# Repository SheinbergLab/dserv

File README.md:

# dserv

## Overview

dserv is a real-time datapoint server for experimental control and data acquisition. At its core is a shared datapoint store (the "bus") implemented in C/C++ that acts as the central communication hub. Attached subprocesses, each running an isolated Tcl interpreter, can listen to, subscribe to, update, and react to changes in datapoints on the bus. This architecture provides extensive scriptability while retaining high-performance C/C++ internals.

All dserv instances include built-in HTTP and WebSocket support. Each instance advertises itself on its own link as a `_dserv._tcp` DNS-SD service (mDNS, via the OS responder) and heartbeats to a workgroup registry for discovery off-link; see `docs/discovery.md`. Web dashboards provide inspection and control of active systems.

## Architecture

```
                        ┌──────────────────────────┐
                        │     Datapoint Store      │
                        │        (the bus)         │
                        └───┬───┬───┬───┬───┬──────┘
                            │   │   │   │   │
               ┌─────────┬──┘   │   │   │   └──┬──────────┐
               │         │      │   │   │      │          │
            ┌──┴──┐  ┌───┴──┐ ┌─┴─┐ │ ┌─┴──┐ ┌─┴──┐  ┌───┴───┐
            │ ess │  │ mesh │ │ em│ │ │stim│ │ df │  │configs│
            └─────┘  └──────┘ └───┘ │ └────┘ └────┘  └───────┘
                                    │
                          ... more subprocesses ...
```
Datapoints are generic data stores that can point to one or more elements of a particular datatype (bytes, short and long integers, strings, floating point and double precision numbers, images, etc. 

Each subprocess is an isolated Tcl interpreter that has direct shared memory access to the datastore. Subprocesses can send messages to other subprocesses and communicate with remote dserv instances over TCP/IP. The startup configuration (`config/dsconf.tcl`) launches the standard set of subprocesses for experiment control, data management, mesh networking, and more.

### Core (`src/`)

The C/C++ core provides:
- **Datapoint store**: thread-safe key-value store with publish/subscribe semantics
- **Datapoint processors**: native C plugins for low-latency datapoint transformations
- **TclServer**: embedded Tcl interpreters for each subprocess with access to the bus
- **HTTP/WebSocket server**: built-in web server for GUIs and API access

### Modules (`modules/`)

Loadable shared libraries that extend subprocess capabilities with hardware and system integration:

| Module | Description |
|--------|-------------|
| `ain` | Analog input |
| `camera` | Camera capture (libcamera) |
| `eventlog` | Event logging |
| `gpio_input` / `gpio_output` | GPIO pin control |
| `ina226` | Power/current monitoring |
| `joystick4` | Joystick input |
| `juicer` | Pump/reward control |
| `mesh` | Mesh network communication |
| `rmt` | Remote stimulus display control |
| `sound` | Audio playback |
| `timer` | Precision timing |
| `touch` | Touchscreen input |
| `usbio` | USB I/O devices |

### Processors (`processors/`)

Native C plugins loaded into the datapoint bus for fast, low-latency processing. These run in the bus thread itself and are used for tasks that require deterministic timing:

- **windows / touch_windows**: define virtual spatial windows and track entry/exit events for eye or touch position data
- **sampler**: datapoint sampling/decimation
- **in_out**: binary region membership testing
- **up_down_left_right**: directional movement detection

### Configuration (`config/`)

Tcl scripts that configure and launch subprocesses. `dsconf.tcl` is the main startup script that initializes the system, loading subprocesses for experiment control (`ess`), eye tracking (`em`), reward delivery (`juicer`), stimulus control (`stim`), data file management (`df`), mesh networking (`mesh`), and others.

### Localization (`local/`)

Local configuration files allow each instance to be customized depending on attached hardware or software requirements. The `local/` folder includes example `.tcl` configuration files that can be copied and customized (removing the .EXAMPLE suffix). These will be maintained across dserv updates.

### Web Interfaces (`www/`)

Browser-based GUIs served by the built-in HTTP server:

- **Dashboard** (`index.html`) - system overview and terminal access
- **ESS Control** (`ess_control.html`) - experiment state system control
- **ESS Workbench** (`ess_workbench.html`) - experiment design and monitoring
- **Data Manager** (`data_manager.html`) - data file management
- **DG Table Viewer** (`DGTableViewer.html`) - data group inspection
- **StimDG Viewer** (`stimdg_viewer.html`) - stimulus data group viewer
- **Event Viewer** (`event_viewer.html`) - real-time event stream
- **Explorer** (`explorer.html`) - datapoint browser
- **Terminal** (`terminal.html`) - Tcl command terminal
- **Tutorial** (`tutorial.html`) - interactive tutorial

Available web interfaces can be accessed based on the names above, as in:

-* http://localhost:2565/ (gui)
-* http://localhost:2565/terminal
-* http://localhost:2565/explorer

### dserv-agent (`dserv-agent/`)

A complementary Go service that provides out-of-band management for dserv systems. Key capabilities:

- **Mesh registry**: aggregates the heartbeats of every dserv in a workgroup, so instances can be found from off-link (on-link discovery is mDNS, see `docs/discovery.md`)
- **Script browsing**: browse and manage experiment scripts
- **Registry mode**: agents can run as registries that store and serve experiment scripts for connected dserv systems
- **Service management**: start/stop/restart dserv, install updates, and monitor health even when dserv is down

### dservctl CLI (`tools/dservctl`)

A command line program called `dservctl` provides a single executable (written in Go) that can be run from the terminal to interact with the dserv process and other subprocesses and to retrieve and update scripts on a dserv-agent registry server. Extensive help is available by running `dservctl --help`.

## Default Endpoints

| Port | Service |
|------|---------|
| 2560 | dserv TCP/IP message port |
| 2565 | dserv WebSocket (dashboard + GUIs) |

## Git Submodules

This repo uses [git submodules](https://git-scm.com/book/en/v2/Git-Tools-Submodules) for several dependencies:
 - [tcl](https://github.com/tcltk/tcl) 9
 - [jansson](https://github.com/akheron/jansson) JSON
 - [FLTK](https://github.com/fltk/fltk) GUI framework

To clone with submodules:

```
git clone --recurse-submodules https://github.com/SheinbergLab/dserv.git
```

To update submodules in an existing clone:

```
git submodule update --init --recursive
git pull --recurse-submodules
```

## Building

dserv uses CMake:

```
mkdir build && cd build
cmake ..
make
```

## Releases with GitHub Actions

This repo uses GitHub Actions to build and test on push, and to create releases on tag push. To release:

```
git tag -a 0.0.2 -m "Release description"
git push --tags
```

See [package_and_release.yml](./.github/workflows/package_and_release.yml) for workflow details and [Releases](https://github.com/SheinbergLab/dserv/releases) for artifacts.

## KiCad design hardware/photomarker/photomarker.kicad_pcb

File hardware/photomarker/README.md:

# Stimulus onset photo-marker

Sheinberg Lab — **rev A**

A per-rig photodiode board that timestamps stimulus light onset two ways at once:
an **analog waveform** into an MCP3204 channel, and a **comparator edge** into a
dserv DI pin (IRQ-latched with a box-clock stamp, so it beats the ~100 µs ADC
scan quantization).

Wire both. The digital edge is your routine per-trial timestamp; the analog
trace is how you verify the edge means what you think, because a fixed voltage
threshold lands at a different fraction of the transition for black→white than
for a gray-to-gray change.

- **50 × 34 mm**, 2-layer, M3 mounts on a **40 × 24 mm** pattern
- Silkscreen carries the lab name and **rev**; bump `REV` in `gen_photomarker.py`
- **DRC clean**: 0 violations, 0 unconnected (KiCad 10.0.4)
- Photodiode die centre is at board-local **(14, 17) mm**, marked with a
  crosshair on both silkscreens so an aperture or hood can be aligned to it

## Regenerating

The board is generated, not hand-drawn. Edit `gen_photomarker.py` (placement
table + routing table near the top) and re-run:

```bash
/Applications/KiCad/KiCad.app/Contents/Frameworks/Python.framework/Versions/3.9/bin/python3 gen_photomarker.py
```

Two API gotchas baked into the script, both found the hard way:
`board.Add(fp)` **must precede** `fp.Flip()` (flipping an unparented footprint
segfaults), and the flip is an **X-mirror** — verified empirically rather than
assumed.

## Board sides

**Top faces the screen.** Only the OPT101 is up there, standing 4.19 mm proud so
nothing shadows it.

**Bottom carries all SMD** — single-sided assembly at JLCPCB, and the board
itself blocks the bring-up LED's light from reaching the photodiode.

## Ordering

Upload `fab/photomarker-gerbers.zip`. For assembly add
`fab/photomarker-cpl.csv` and `fab/photomarker-bom.csv`.

**The BOM's `LCSC Part #` column is deliberately empty.** Fill it from JLCPCB's
parts search — do not trust a guessed C-number, it orders the wrong part.

JLCPCB places **10 parts**: U2, R1–R5, R11, C1–C3. Everything else is DNP or
hand-soldered. At that count, hand-soldering a SOIC-8 and nine 0805s may well
cost less than the assembly setup fee — worth pricing both ways.

### You solder these yourself

| Ref | Part | Note |
|-----|------|------|
| U1 | OPT101, DIP-8 | Mount from the **top**. Strap pin 4 (1M) to pin 5 (OUT) is on the PCB already. |
| J1 | JST-PH B5B-PH-K, 5-pin vertical | On the bottom, so the cable exits away from the screen. |

**OPT101 handling:** TI warns the clear plastic is moisture-sensitive and that
rapid heating can stress the wire bonds. If the parts have sat in humidity, bake
at 85 °C for 24 h first. Solder gently either way.

## Connector J1

Pin 1 is leftmost. Silkscreen reads `3V3 GND AO DIb DIa`.

| Pin | Net | To the extio box |
|-----|-----|------------------|
| 1 | +3V3 | 3V3 |
| 2 | GND | GND |
| 3 | AOUT | MCP3204 **CH2** (CH0/CH1 are the joystick) |
| 4 | DI-B | free GPIO — optional second threshold |
| 5 | DI-A | free GPIO — **main onset edge** |

Free GPIOs per `wiznet-io/PINMAP.md`: 9–14, 26, 27.

**Output goes LOW on light onset** (signal on IN−), so configure that DI for the
falling edge.

On the `ain` group carrying CH2: set `deadband 0` and `average 1`. Both smear
the edge, which is the one thing you are trying to measure.

## Design values

Threshold network on 3.3 V, R1 = 39 k, R2 = 10 k, R3 = 270 k:

- Onset threshold **0.749 V**, release **0.654 V**, hysteresis **94 mV**
- Input filter R4/C3 = 10 k / 3.3 nF → **4.8 kHz**, τ = 33 µs

Because the signal is on IN−, **the hysteresis lands entirely on the release
side** — it costs nothing on the onset edge, so be generous with it.

Aim the threshold at **~50 % of your lit-state level**, not 20 %. Mid-transition
is steepest, so timing there is least sensitive to stimulus amplitude drift. The
resulting latency to true onset is a constant: measure it once off the analog
trace and subtract.

Retune by swapping R1 alone:

| R1 | Onset | Hysteresis |
|----|-------|-----------|
| 68 k | 0.513 V | 103 mV |
| **39 k** | **0.749 V** | **94 mV** |
| 27 k | 0.955 V | 87 mV |
| 18 k | 1.228 V | 77 mV |
| 12 k | 1.536 V | 65 mV |

C3 must be **C0G/NP0**, not X7R — X7R drifts with temperature and DC bias, which
would move the filter corner and turn your calibrated constant lag into a
drifting one.

## U2: TLV3202 or LM393

The footprint is SOIC-8 and the two parts are pin-identical
(1=OUT_A, 2=IN_A−, 3=IN_A+, 4=GND, 5=IN_B+, 6=IN_B−, 7=OUT_B, 8=VCC).

- **TLV3202** (recommended): push-pull, 5 mV max offset. Leave R7/R14 unfitted.
- **LM393** (fallback): open-collector — **fit R7** (and R14 if using
  comparator B) as pull-ups to 3.3 V.

The LM393's common-mode ceiling (V+ − 1.5 V ≈ 1.8 V at 3.3 V) is not a problem
at this operating point, since the threshold is 0.749 V and the lit level is
~1.5 V by design. There is no 5 V anywhere on the board, so nothing can put 5 V
on a GPIO.

## DNP options

| Ref | Purpose |
|-----|---------|
| R6 | External gain resistor across the OPT101 feedback — **fit this if you saturate**, which is likely at 0.45 V/µW |
| R8 | Parallel with R1 for fine threshold trim |
| R7, R14 | Pull-ups, LM393 only |
| R9, D1 | Bring-up LED on the comparator output. D1 pin 1 = **cathode** (KiCad convention), so the anode faces R9 / +3V3 and the LED lights when the output goes low on light onset |
| R12, R13, R15 | Comparator B's second threshold → DI-B. Populate to time the 25 %→75 % crossing and measure the panel's transition slope in hardware, per trial |
| J2 | 0.1" alternative to J1, same pinout |

**R11 (10 k) is fitted, not DNP.** With the B network unpopulated it pulls
comparator B's IN+ to 3.3 V — definitively above IN−'s ~2.0 V ceiling — so that
comparator parks HIGH instead of oscillating on a floating input, and DI-B
carries a defined level. Re-value it into a real divider with R12 when you
actually want the second threshold.

## Bring-up

Test points: TP1 OPT_OUT, TP2 FILT, TP3 THRESH, TP4 CMP_OUT, TP5 GND.

1. **Cover the sensor.** TP1 should read ~7.5 mV. Mid-scale or railed means the
   part is wrong or damaged.
2. **TP3 should read 0.749 V.**
3. **Point at a white screen.** If TP1 pins at ~2.0 V you are saturated — fit R6,
   mask down to a smaller aperture, or back off.
4. **Check for backlight PWM on the analog channel before trusting anything.** A
   few-hundred-Hz chop cannot be filtered out without wrecking a 2 ms edge. Run
   the panel at 100 % brightness, where most panels stop PWM-ing. Only if you're
   stuck with it, raise C3 to 22 nF (720 Hz, τ = 220 µs) and accept the larger
   constant lag.

## Schematic

`photomarker.kicad_sch` + `schematic.pdf`. **ERC clean (0 violations)**, and verified
against the board by `check_netlist.py` — which compares **nets, refs, values,
footprints and DNP flags**, not just connectivity. All 12 nets match exactly; the
only schematic-side extras are the OPT101's two NC pins, deliberately unconnected
on both sides.

Run it before ordering and after any regeneration (exit status 0 = agreement):

```bash
/Applications/KiCad/KiCad.app/Contents/Frameworks/Python.framework/Versions/3.9/bin/python3 check_netlist.py
```

It is generated by `gen_schematic.py`, which **reads the netlist out of
`photomarker.kicad_pcb`** — so the schematic cannot silently drift from the
board. Regenerate after any board change:

```bash
/Applications/KiCad/KiCad.app/Contents/Frameworks/Python.framework/Versions/3.9/bin/python3 gen_schematic.py
```

Connectivity is by net label rather than drawn wire, with components grouped by
function. That is a deliberate choice for a generated schematic: label
connectivity is verifiable by ERC and by netlist diff, where hand-computed wire
geometry can look connected while being 0.01 mm short.

### Custom symbols

KiCad ships neither part, so `photomarker.kicad_sym` defines both:

- **OPT101** — DIP-8, drawn as photodiode + transimpedance amp. Pins 6 and 7 are
  genuinely NC and carry no-connect flags.
- **TLV3202** — 3 units (A, B, power). Built on KiCad's LM2903 geometry, since
  the pinout is identical, but with `output` pins instead of `open_collector`.

`sym-lib-table` maps `photomarker:` to the local library, so the project opens
standalone.

### What the schematic caught

Drawing it found a **real bug in the board**: KiCad's `Device:LED` has **pin 1 =
cathode**, but D1 pin 1 had been wired to the resistor from +3V3 — the indicator
LED was reverse-biased. Fixed by swapping the net assignment and flipping D1.
Worth remembering if you add any other polarised part.

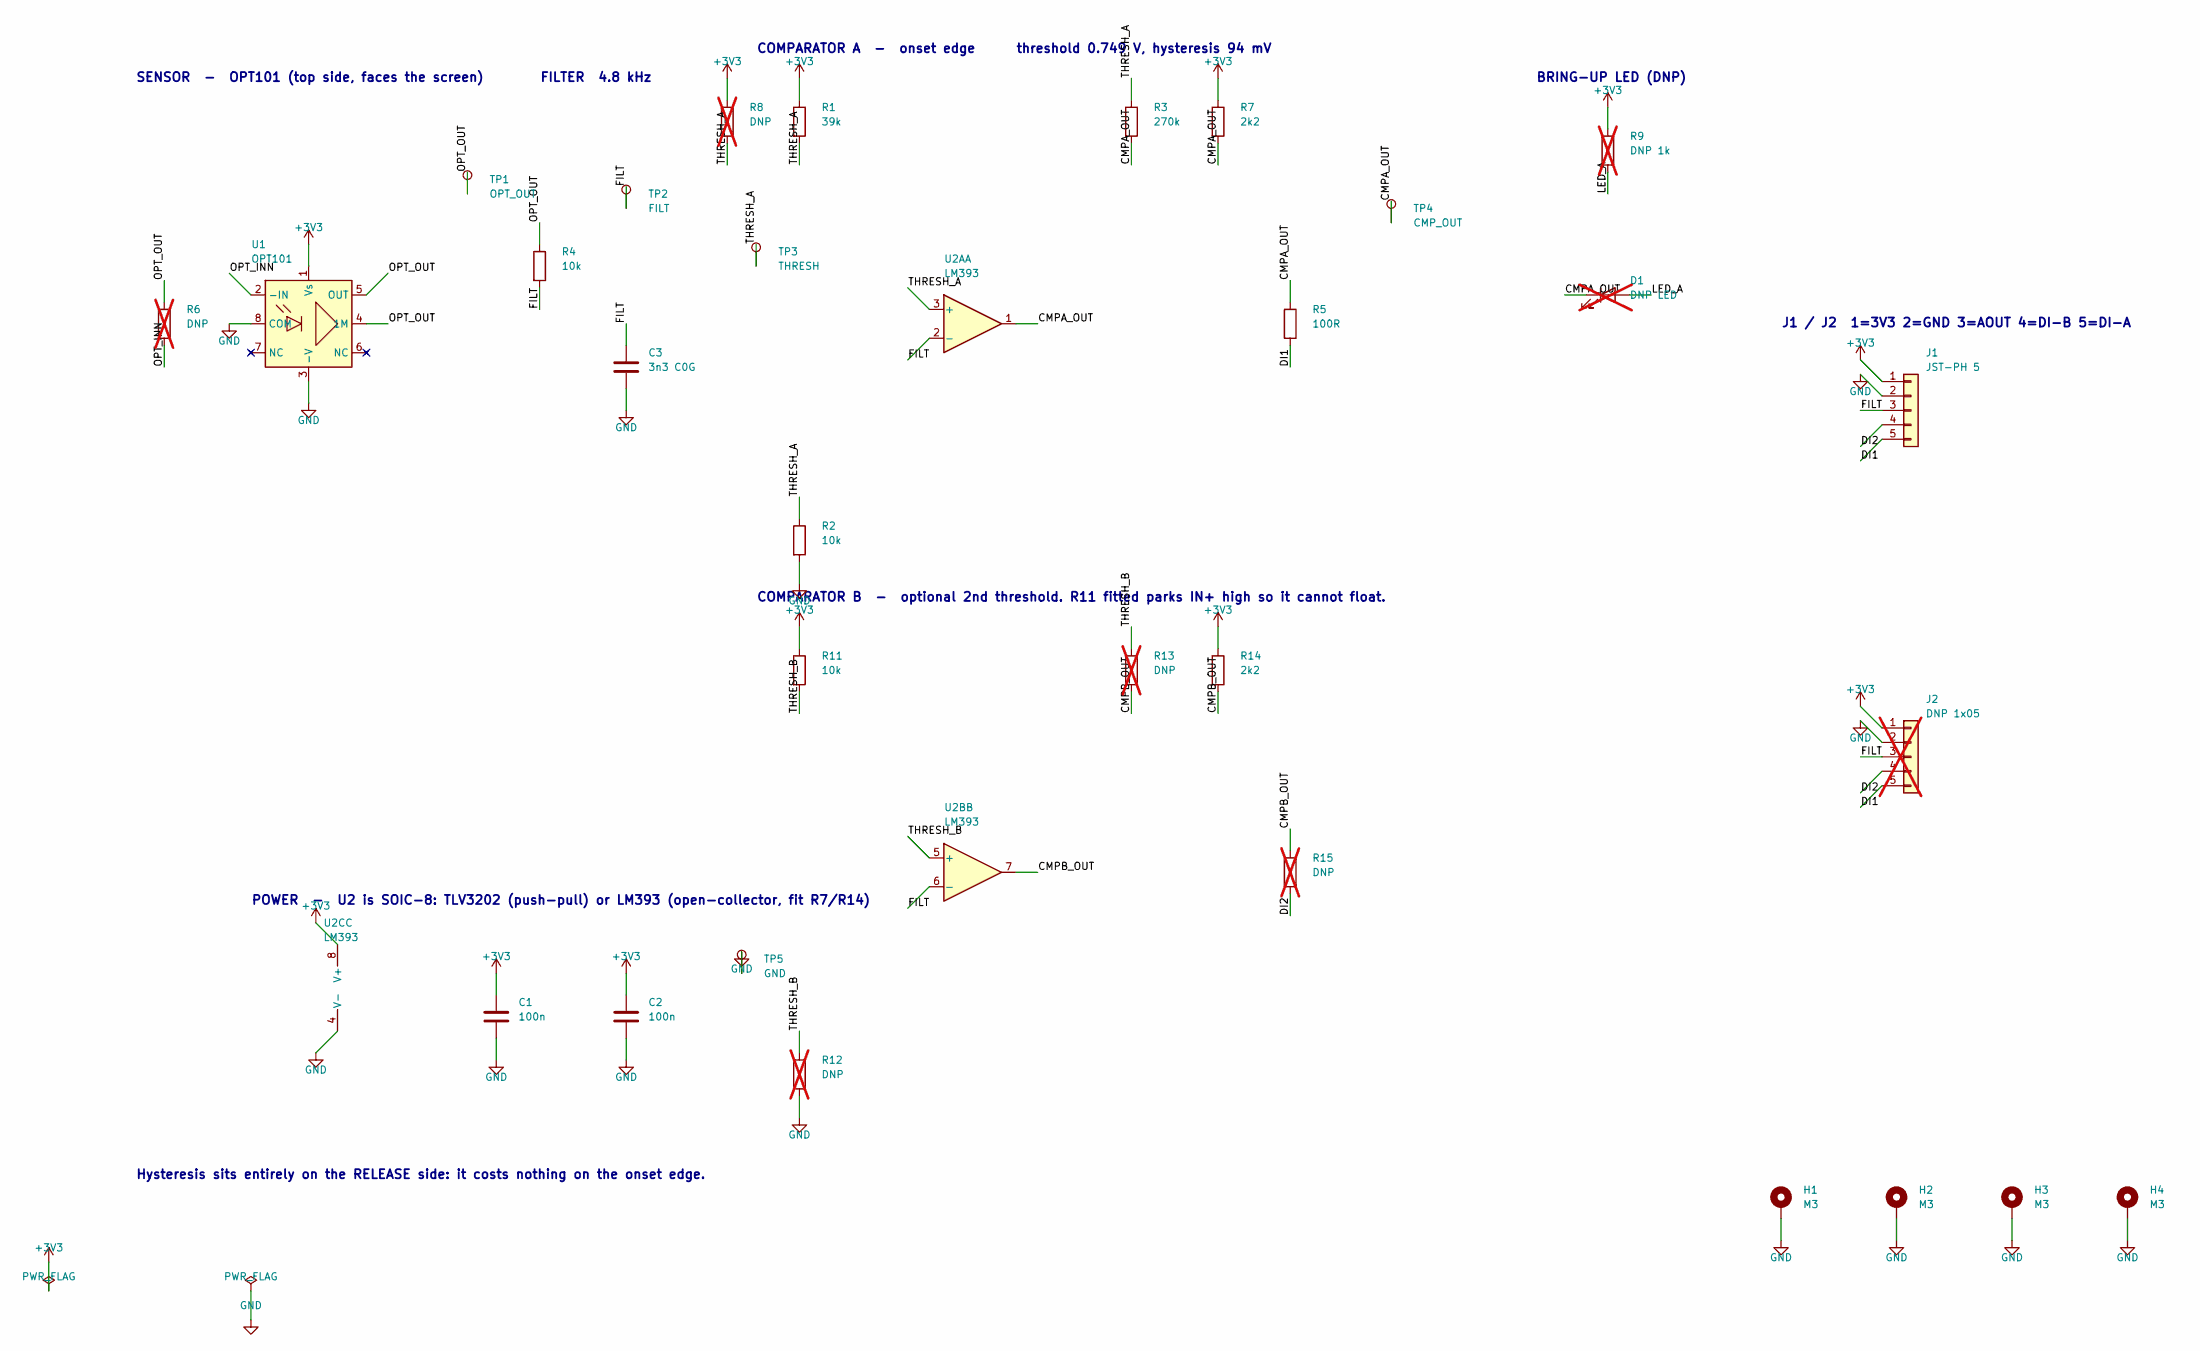
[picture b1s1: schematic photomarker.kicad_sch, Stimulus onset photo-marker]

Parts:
C1, C2: 100n; C_0805_2012Metric
C3: 3n3 C0G; C_0805_2012Metric
D1: DNP LED; LED_0805_2012Metric; not fitted
H1, H2, H3, H4: M3; MountingHole_3.2mm_M3_Pad
J1: JST-PH 5; JST_PH_B5B-PH-K_1x05_P2.00mm_Vertical
J2: DNP 1x05; PinHeader_1x05_P2.54mm_Vertical; not fitted
R1: 39k; R_0805_2012Metric
R2, R4, R11: 10k; R_0805_2012Metric
R3: 270k; R_0805_2012Metric
R5: 100R; R_0805_2012Metric
R6, R8, R12, R13, R15: DNP; R_0805_2012Metric; not fitted
R7, R14: 2k2; R_0805_2012Metric
R9: DNP 1k; R_0805_2012Metric; not fitted
TP1: OPT_OUT; TestPoint_THTPad_D1.5mm_Drill0.7mm
TP2: FILT; TestPoint_THTPad_D1.5mm_Drill0.7mm
TP3: THRESH; TestPoint_THTPad_D1.5mm_Drill0.7mm
TP4: CMP_OUT; TestPoint_THTPad_D1.5mm_Drill0.7mm
TP5: GND; TestPoint_THTPad_D1.5mm_Drill0.7mm
U1: OPT101; DIP-8_W7.62mm
U2A, U2B, U2C: LM393; SOIC-8_3.9x4.9mm_P1.27mm

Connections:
+3V3: C1.1, C2.1, J1.1, J2.1, R1.1, R7.1, R8.1, R9.1, R11.1, R14.1, U1.1 (Vs); also elsewhere on the board
CMPA_OUT: D1.1 (K), R3.2, R5.1, R7.2, TP4.1; also elsewhere on the board
CMPB_OUT: R13.2, R14.2, R15.1; also elsewhere on the board
DI1: J1.5, J2.5, R5.2
DI2: J1.4, J2.4, R15.2
FILT: C3.1, J1.3, J2.3, R4.2, TP2.1; also elsewhere on the board
GND: C1.2, C2.2, C3.2, H1.1, H2.1, H3.1, H4.1, J1.2, J2.2, R2.2, R12.2, TP5.1, U1.3 (-V), U1.8 (COM); also elsewhere on the board
LED_A: D1.2 (A), R9.2
OPT_INN: R6.2, U1.2 (-IN)
OPT_OUT: R4.1, R6.1, TP1.1, U1.4 (1M), U1.5 (OUT)
THRESH_A: R1.2, R2.1, R3.1, R8.2, TP3.1; also elsewhere on the board
THRESH_B: R11.2, R12.1, R13.1; also elsewhere on the board

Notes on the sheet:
SENSOR - OPT101 (top side, faces the screen)
FILTER 4.8 kHz
COMPARATOR A - onset edge threshold 0.749 V, hysteresis 94 mV
COMPARATOR B - optional 2nd threshold. R11 fitted parks IN+ high so it cannot float.
POWER - U2 is SOIC-8: TLV3202 (push-pull) or LM393 (open-collector, fit R7/R14)
BRING-UP LED (DNP)
J1 / J2 1=3V3 2=GND 3=AOUT 4=DI-B 5=DI-A
Hysteresis sits entirely on the RELEASE side: it costs nothing on the onset edge.

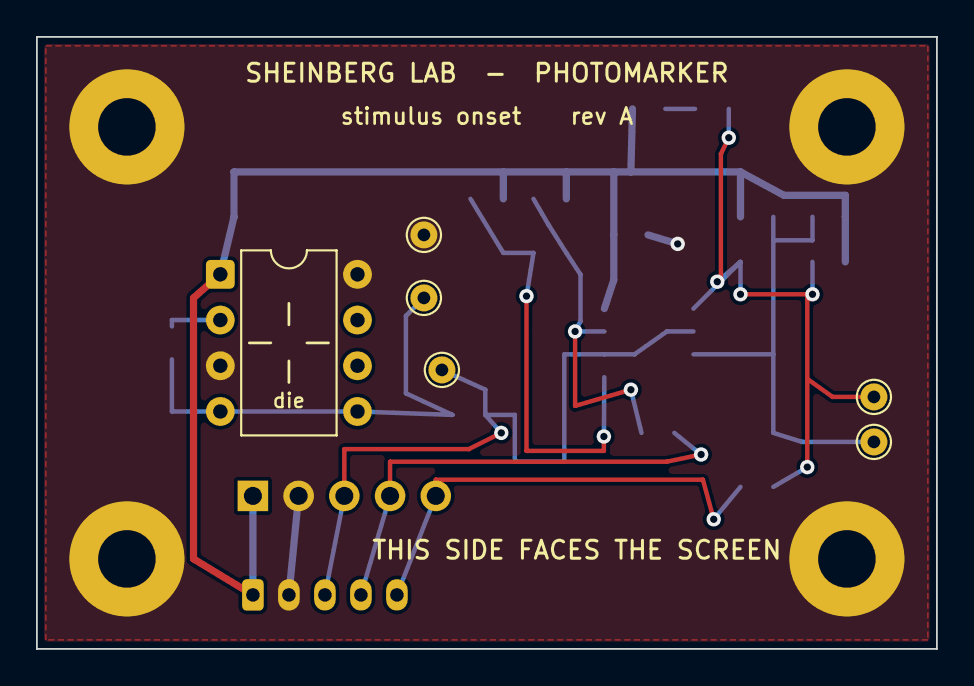
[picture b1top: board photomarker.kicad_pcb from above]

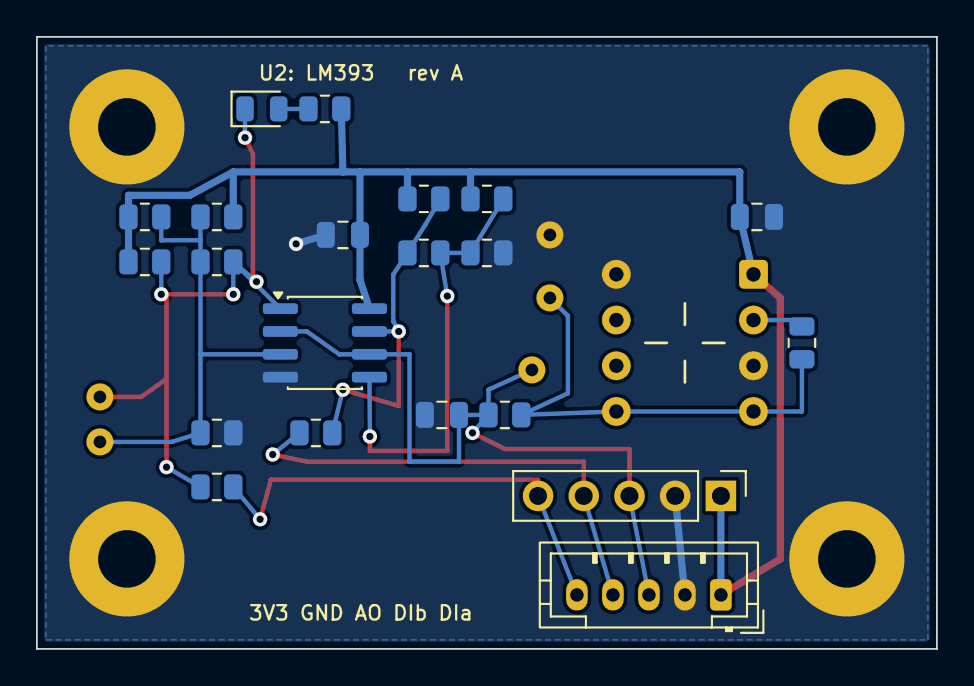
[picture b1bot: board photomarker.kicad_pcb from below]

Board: 2 copper layers, 50.0 x 34.0 mm, 31 parts (21 on the bottom side), 12 nets.

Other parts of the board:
U2: LM393; SOIC-8_3.9x4.9mm_P1.27mm

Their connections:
+3V3: U2.8; also elsewhere on the board
CMPA_OUT: U2.1; also elsewhere on the board
CMPB_OUT: U2.7; also elsewhere on the board
FILT: U2.2, U2.6; also elsewhere on the board
GND: U2.4; also elsewhere on the board
THRESH_A: U2.3; also elsewhere on the board
THRESH_B: U2.5; also elsewhere on the board

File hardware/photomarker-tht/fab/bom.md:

# Mouser BOM - photomarker rev B (through-hole)

For **5 boards**, hand-assembled. Quantities include spares.

`OK` = verified listing. `CHECK` = derived from the maker's scheme, confirm in the cart. `PICK` = you must choose one.

| Qty | Value | Designators | Mfr part | Mfr | ? | Note |
|----:|-------|-------------|----------|-----|---|------|
| 10 | 100R | R5 | `MFR-25FBF52-100R` | Yageo | CHECK | 1% |
| 20 | 100n | C1,C2 | `K104K15X7RF5UH5` | Vishay | CHECK | 100nF 50V X7R disc, 5mm pitch. Any 0.1uF THT is fine. |
| 26 | 10k | R1,R11,R2,R4 | `MFR-25FBF52-10K` | Yageo | CHECK | 1% |
| 10 | 270k | R3 | `MFR-25FBF52-270K` | Yageo | CHECK | 1% |
| 10 | 2k2 | R7 | `MFR-25FBF52-2K2` | Yageo | CHECK | 1% |
| 10 | 3n3 C0G | C3 | `FKP2D013301G00JSSD` | WIMA | OK | 3.3nF 100V +-2% polypropylene film, 5mm pitch. Film is the easy THT answer here; a C0G/NP0 ceramic is equally fine. NEVER X7R -- it drifts with temperature and DC bias and would turn the calibrated lag into a drifting one. |
| 6 | 50k | RV1 | `3296W-1-503LF` | Bourns | OK | 25-turn cermet trimmer, top adjust. |
| 10 | JST-PH 5 | J1 | `B5B-PH-K-S(LF)(SN)` | JST | CHECK | 5-pin PH vertical header, board side. |
| 10 | LM393 | U2 | `LM393P` | TI | CHECK | DIP-8. LM393N is the onsemi equivalent. |
| 10 | OPT101 | U1 | `OPT101P` | TI | OK | 8-DIP clear. Legacy THT analog part -- buy deep. |
| 10 | DIP-8 socket | - | `1-2199298-2` | TE | CHECK | One each for U1 and U2. Keeps soldering heat off the OPT101 entirely. |
| 5 | PH housing | - | `PHR-5` | JST | CHECK | Cable-side mating shell for J1. |
| 25 | PH crimps | - | `SPH-002T-P0.5S` | JST | CHECK | 22-28 AWG. Needs the right crimp tool -- else buy ready-made pigtails. |

## Not populated (DNP)

Buy only if you want the option.

- **J2, R12, R13, R14, R15, R6** - DNP

R6 is the OPT101 gain resistor: **pick its value after seeing TP1 on a real screen**, not now.
